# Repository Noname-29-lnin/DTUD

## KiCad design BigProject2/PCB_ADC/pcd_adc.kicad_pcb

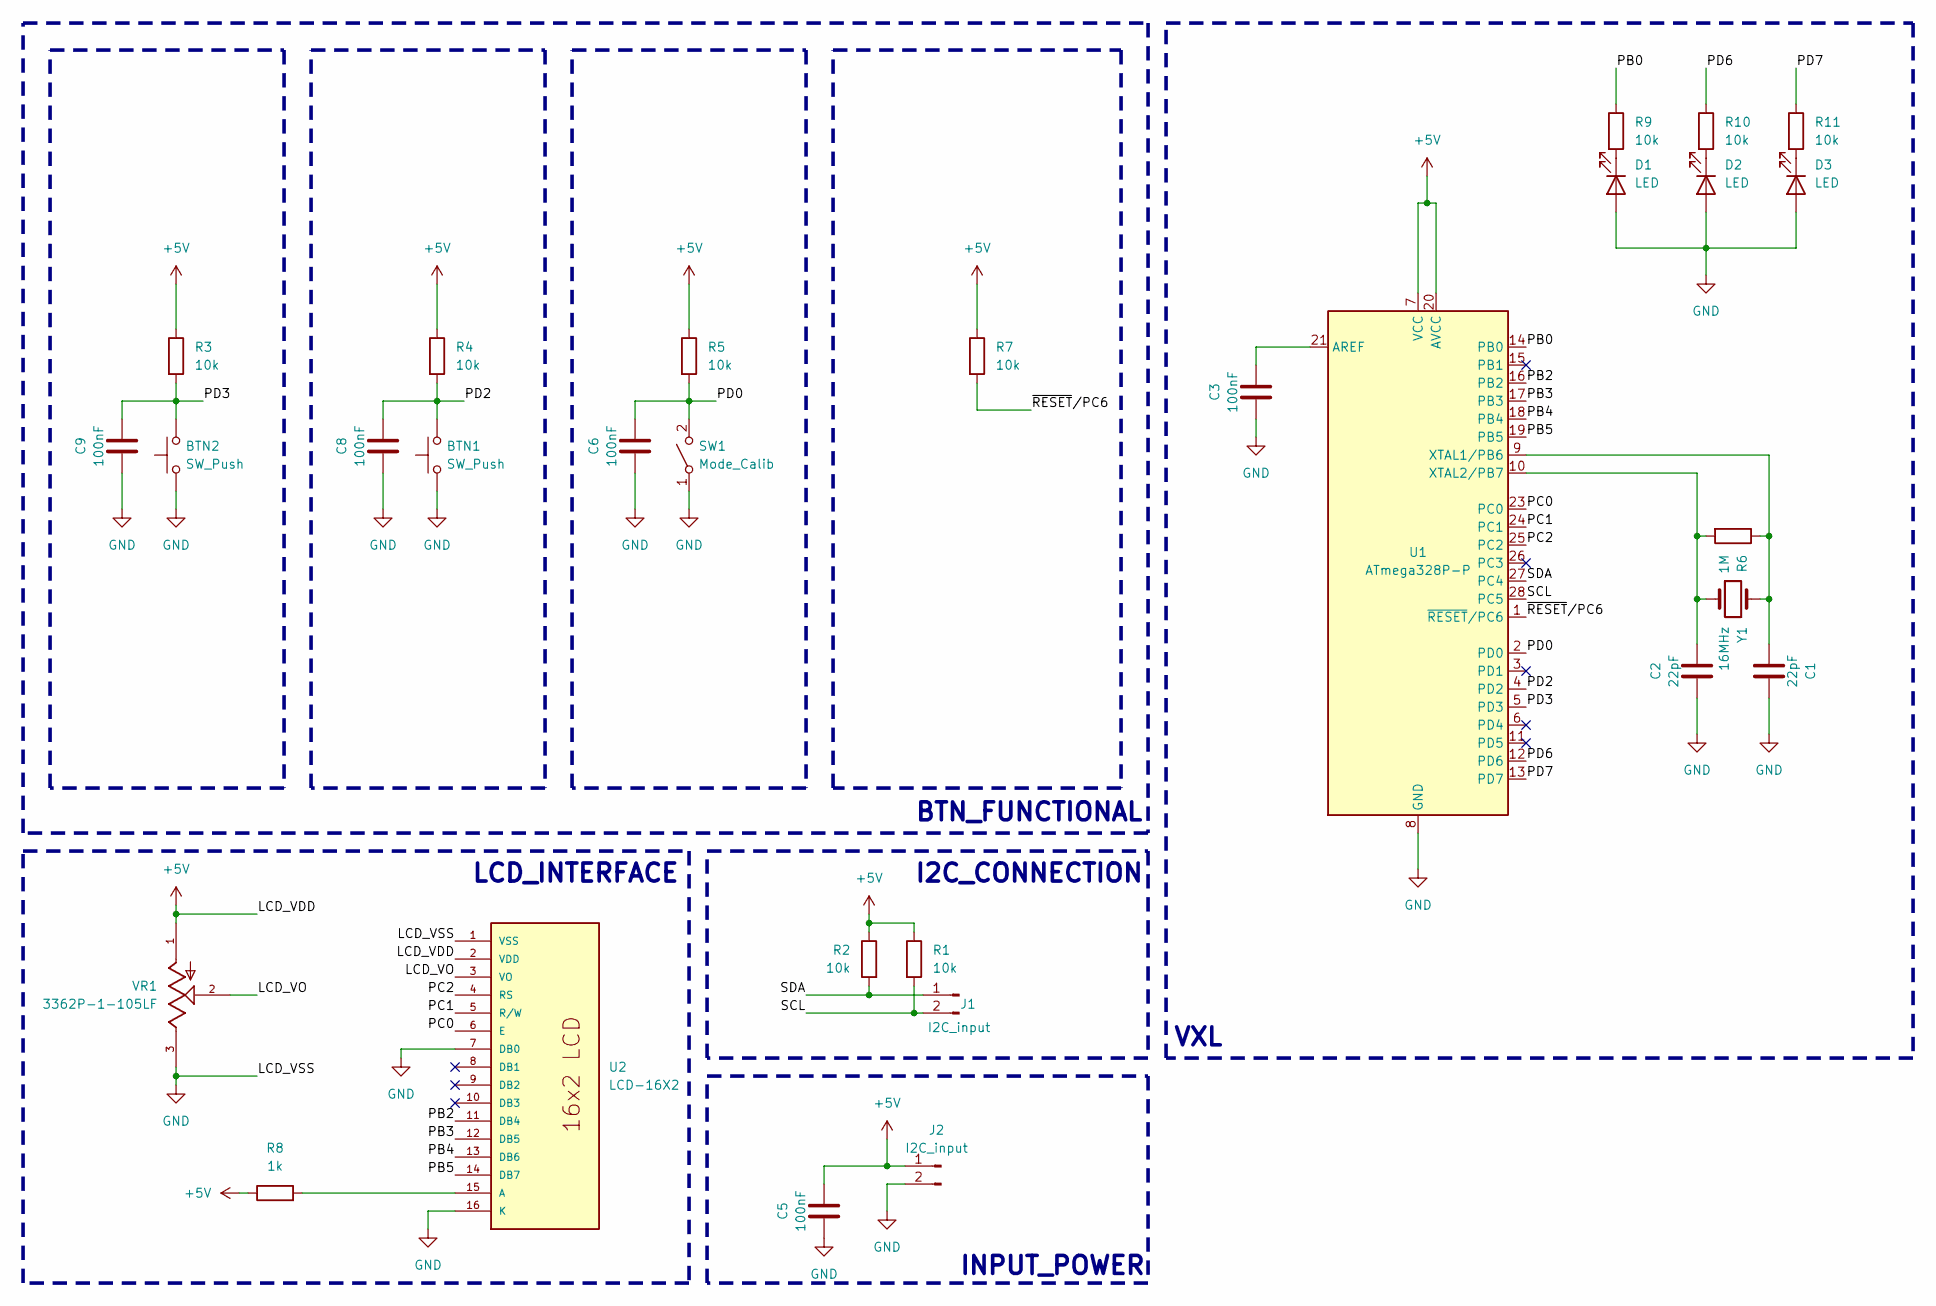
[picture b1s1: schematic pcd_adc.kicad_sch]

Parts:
BTN1, BTN2: SW_Push; SW_PUSH-12mm_Wuerth-430476085716
C1, C2: 22pF; R_1206_3216Metric
C3: 100nF; C_1206_3216Metric
C5, C6, C8, C9: 100nF; C_Disc_D7.5mm_W5.0mm_P7.50mm
D1, D2, D3: LED; LED_0805_2012Metric
J1: I2C_input; PinHeader_1x02_P2.54mm_Horizontal
J2: I2C_input; Samtec_HPM-02-05-x-S_Straight_1x02_Pitch5.08mm
R1, R2, R3, R4, R5, R7: 10k; R_Axial_DIN0207_L6.3mm_D2.5mm_P10.16mm_Horizontal
R6: 1M; R_1206_3216Metric
R8: 1k; R_1206_3216Metric
R9, R10, R11: 10k; R_1206_3216Metric
SW1: Mode_Calib; SW_DIP_SPSTx01_Slide_Omron_A6S-110x_W8.9mm_P2.54mm
U1: ATmega328P-P; DIP-28_W7.62mm
U2: LCD-16X2; MODULE_LCD-16X2; PARTREV N/A
VR1: 3362P-1-105LF; TRIM_3362P-1-105LF; PARTREV 08/26/10
Y1: 16MHz; Crystal_HC49-4H_Vertical

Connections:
+5V: C5.2, J2.1, R1.1, R2.1, R3.1, R4.1, R5.1, R7.1, R8.1, U1.7 (VCC), U1.20 (AVCC), U2.2 (VDD), VR1.1
/LCD_VO: U2.3 (VO), VR1.2
/PB0: R9.1, U1.14 (PB0)
/PB2: U1.16 (PB2), U2.11 (DB4)
/PB3: U1.17 (PB3), U2.12 (DB5)
/PB4: U1.18 (PB4), U2.13 (DB6)
/PB5: U1.19 (PB5), U2.14 (DB7)
/PC0: U1.23 (PC0), U2.6 (E)
/PC1: U1.24 (PC1), U2.5 (R/W)
/PC2: U1.25 (PC2), U2.4 (RS)
/PD0: C6.2, R5.2, SW1.2 (B), U1.2 (PD0)
/PD2: BTN1.2, C8.2, R4.2, U1.4 (PD2)
/PD3: BTN2.2, C9.2, R3.2, U1.5 (PD3)
/PD6: R10.1, U1.12 (PD6)
/PD7: R11.1, U1.13 (PD7)
/SCL: J1.2, R1.2, U1.28 (PC5)
/SDA: J1.1, R2.2, U1.27 (PC4)
/~RESET/PC6: R7.2, U1.1 (~RESET/PC6)
GND: BTN1.1, BTN2.1, C1.2, C2.1, C3.1, C5.1, C6.1, C8.1, C9.1, D1.2 (A), D2.2 (A), D3.2 (A), J2.2, SW1.1 (A), U1.8 (GND), U1.22 (GND), U2.1 (VSS), U2.7 (DB0), U2.16 (K), VR1.3
unnamed: D1.1 (K), R9.2
unnamed: D2.1 (K), R10.2
unnamed: D3.1 (K), R11.2
unnamed: C3.2, U1.21 (AREF)
unnamed: C1.1, R6.1, U1.9 (XTAL1/PB6), Y1.2
unnamed: C2.2, R6.2, U1.10 (XTAL2/PB7), Y1.1
unnamed: R8.2, U2.15 (A)

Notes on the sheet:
BTN_FUNCTIONAL
I2C_CONNECTION
LCD_INTERFACE
INPUT_POWER
VXL

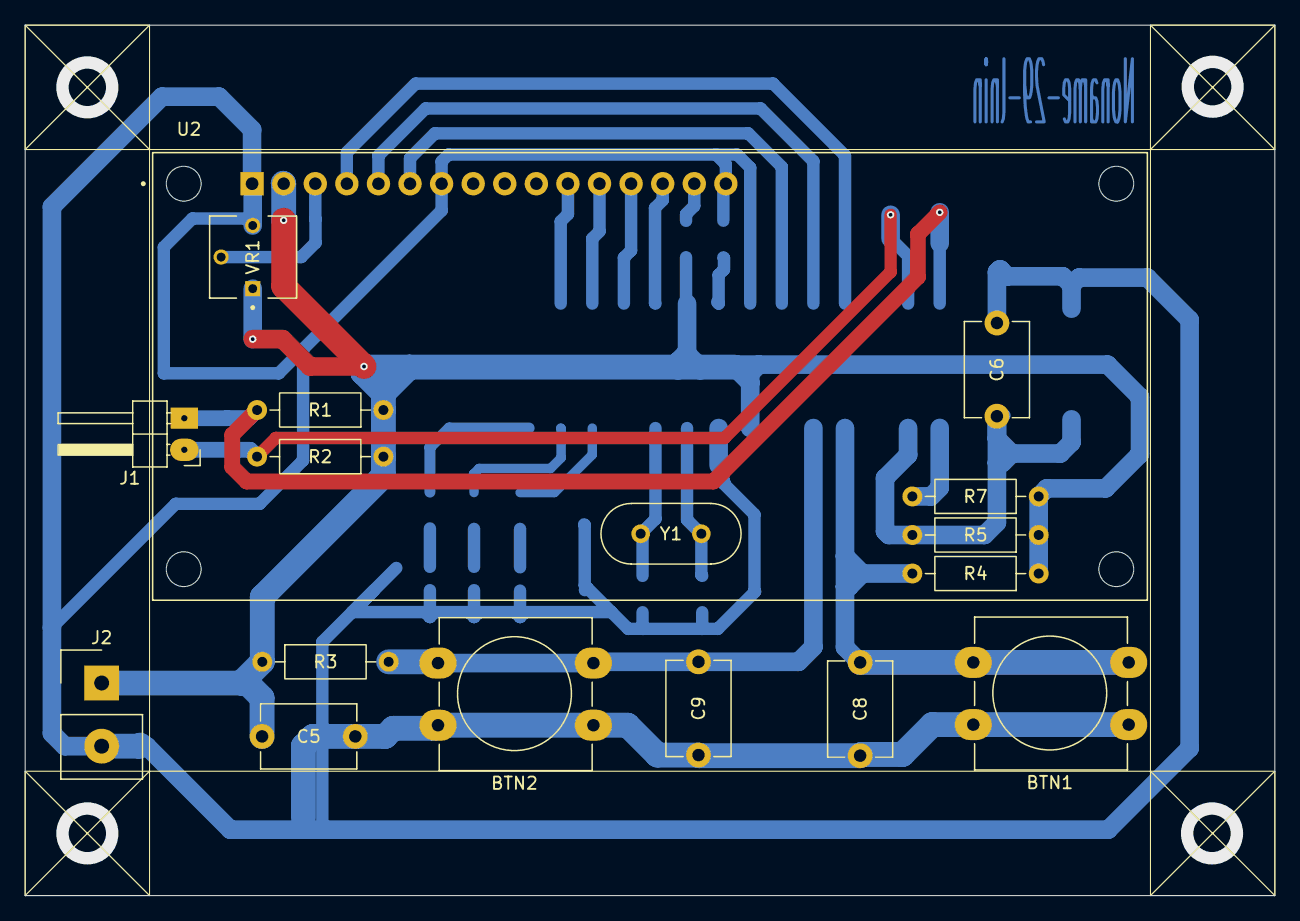
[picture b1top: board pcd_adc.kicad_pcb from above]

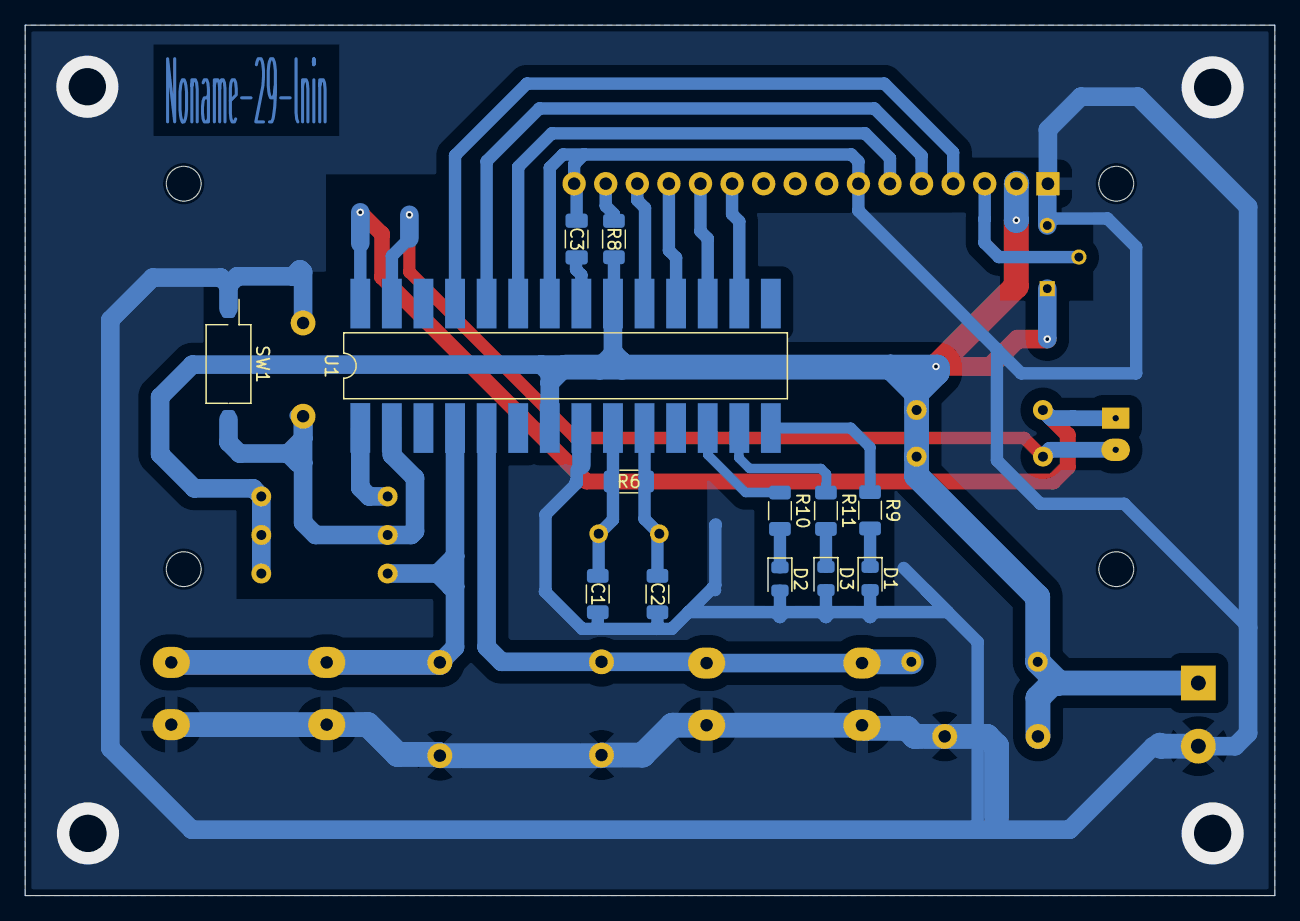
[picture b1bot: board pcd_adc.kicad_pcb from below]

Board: 2 copper layers, 100.5 x 70.0 mm, 30 parts (13 on the bottom side), 26 nets.

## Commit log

2025-10-14 update question 6
2025-10-14 up q10
2025-10-15 update question 4
2025-10-16 up question 5
2025-10-16 update question 5
2025-10-16 up question 9 and question 10
2025-10-17 up question 8
2025-10-17 update question 7
2025-10-18 update question 5 and question 7
2025-10-18 update question 3
2025-10-19 update question 2
2025-10-19 update final report
2025-10-20 update final
2025-10-30 update question 6 homework 2
2025-10-30 update question 6 homework2
2025-10-30 update question 8 homework2
2025-11-02 update question 10, 11, 12, 13, 14
2025-11-02 update question 9
2025-11-06 update question 1234
2025-11-09 up question 1 2 3
2025-11-10 update fin ex2
2025-11-28 up ADC_excel
2025-11-29 up export file ADC
2025-12-04 update bigproject2
2025-12-05 up code ADC
2025-12-07 up pcb adc
2025-12-18 up date PCB
2025-12-24 up code
2025-12-27 up docs bigproject2
2025-12-30 up adc_pcb
2026-01-04 up code final
